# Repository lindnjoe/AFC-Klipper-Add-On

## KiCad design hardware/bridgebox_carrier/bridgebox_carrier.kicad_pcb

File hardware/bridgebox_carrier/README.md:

# BridgeBox carrier — KiCad project

The board described in
[`../../bambu_ams_bridge/docs/CARRIER_BOARD.md`](../../bambu_ams_bridge/docs/CARRIER_BOARD.md).
Read that first: it carries the reasoning, the current budget and the two
measured pinouts. This directory is the implementation.

Built against **KiCad 7**.

```
bridgebox_carrier.kicad_pro   project, netclasses and design rules
bridgebox_carrier.kicad_sch   schematic — generated, see below
bridgebox_carrier.kicad_pcb   board outline and stackup only
bridgebox.kicad_sym            symbols for the two modules
bridgebox.pretty/              footprints for the two modules
gen_project.py                writes the schematic and the symbol library
gen_pcb.py                    places and routes the board
route.py                      the tracks, as explicit polylines
geometry.py                   pad positions, shared by router and checker
verify_netlist.py             checks KiCad's netlist against the design
verify_wiring.py              checks the finished board against the proven pinout
check_placement.py            checks the placement for collisions
check_drc.py                  fast clearance and connectivity pre-check
finish_board.py               fills the ground plane, runs KiCad's real DRC
gen_bom.py                    the two BOMs
gen_cpl.py                    rewrites the placement file into CPL format
build.sh                      does all of it, in the one correct order
case/                         a two-piece printed case for the finished board
```

The case is its own project with its own checker and its own build; see
[`case/README.md`](case/README.md).

## Opening it

Open `bridgebox_carrier.kicad_pro`. Both the schematic and the board are
complete: placed, routed and checked. 367 mm of track, no vias and **no layer
changes at all** — B.Cu is an unbroken ground plane.

The board is 63 × 54 mm, two layers, 1 oz, laid out to the arrangement asked
for:

- **Left edge** — the Pico's USB and J1, the 24 V jack. The Pico is turned 90°
  so it runs inland from that edge with the USB overhanging it.
- **Bottom edge** — J2, the AMS 4-pin, a quarter turn round from them.
- Between them: the RS-485 module stands upright UNDER the Pico, logic pins up
  towards it and bus pins down towards J2, with the fuse in the band between.

**It used to be 84 × 58 mm.** Three things shrank it: the two A/B swap jumpers
came out once the bus wiring was settled on hardware, the module's pad columns
turned out to be 15 mm apart rather than the 0.7 in first assumed, and turning
the module upright moved it out from the Pico's right-hand side, which is what
the extra 21 mm of width had been for. Its bus pins now face J2 instead of
away from it, so A and B no longer lap the board — and the layer hop that used
to cost a slot in the ground plane went with them.

The M3 holes are **not** one per corner: the Pico's body runs the length of the
top edge and J2 owns the bottom middle, so most corners are already taken.

Mounting holes are placed in the board rather than drawn in the schematic,
which is normal for mechanical features — so if you ever re-import from the
schematic, leave "delete extra footprints" unticked or they will vanish.

Everything except the two modules comes from KiCad's stock libraries, including
`Molex_Micro-Fit_3.0_43045-0400_2x02_P3.00mm_Horizontal` for J2, so there is no
land pattern to draw by hand.

## Why the schematic is generated

The connectivity is the part that must not drift from the design document, so
it lives as a table — `NETS` in `gen_project.py` — rather than as geometry.
Regenerate with:

```sh
python3 gen_project.py
kicad-cli sch export netlist --output out/netlist.net bridgebox_carrier.kicad_sch
python3 verify_netlist.py
```

`verify_netlist.py` compares what KiCad *actually extracted* against that
table, pin for pin, and fails on a net that is split, merged or holding a pin
it should not. That matters because the schematic connects by label: a
mistyped label does not break the build, it silently makes two nets where
there should be one. The check is what lets this project be trusted without
opening the GUI.

Editing the schematic in KiCad is fine — but then it is the source, and
re-running the generator will overwrite it.

`verify_wiring.py` is narrower and runs LAST, after `finish_board.py` has
filled the zone and rewritten the file: it checks that the handful of pin
assignments established by measurement rather than by reading a silkscreen —
`GP0 → RXD`, `GP1 → TXD`, the A/B crossover, and J2's 24 V and GND — are the
ones on the pads the gerbers are plotted from. Every one of them is a place
where the obvious answer is wrong and the symptom of being wrong is a bus that
goes silent rather than one that misbehaves visibly.

`check_placement.py` does the same job for the board, comparing every
footprint's courtyard against every other one and against the mounting holes.
A render will not show you these: a mounting hole sitting inside the Pico's
outline just looks like a hole among a lot of pads. It found exactly that, plus
a 0.3 mm overlap between the Pico and the RS-485 module and a TVS sitting on
J2's body — none of which were visible by eye.

## What is still on you

Two things the project deliberately does not decide:

1. **A second pair of eyes on J2's pinout.** It is taken from Molex
   SD-43045-001 and the metered mating face, and it is the one mistake that
   puts 24 V on the transceiver.
2. **The remaining DRC warnings**, which are all cosmetic and all understood:

   | Count | Warning | Why it is left |
   |---|---|---|
   | 7 | `lib_footprint_issues` | this project's `fp-lib-table` lists only `bridgebox`; the stock libraries come from the global table on a normal install |
   | 3 | `silk_edge_clearance` | J2's body outline runs past the bottom edge, which is what a connector mating through that edge looks like; fabs clip silkscreen automatically |
   | 2 | `lib_footprint_mismatch` | the board's copy of the two custom footprints omits the library-only `version`/`generator` keys |

   **Zero errors:** no clearance violations, no unconnected pads, no footprint
   errors.

## Parts with no stock symbol

Both were measured, not taken from a datasheet:

- `RaspberryPi_Pico_THT` — 2×20, 0.1 in pitch, rows 0.7 in apart, pin 1 at the
  USB end.
- `MAX3485_Module_3L5R` — a 2×5 field with two positions empty. **Top view is
  three pins on the left (GND, A, B) and five on the right (EN, VCC, RXD, TXD,
  GND).** The underside reads mirrored; the footprint is the top view.
  0.1 in pitch down each column, columns **15 mm** apart — not the Pico's
  0.7 in. Measured on the part after a first revision built to 17.78 mm came
  back 2.8 mm too wide.

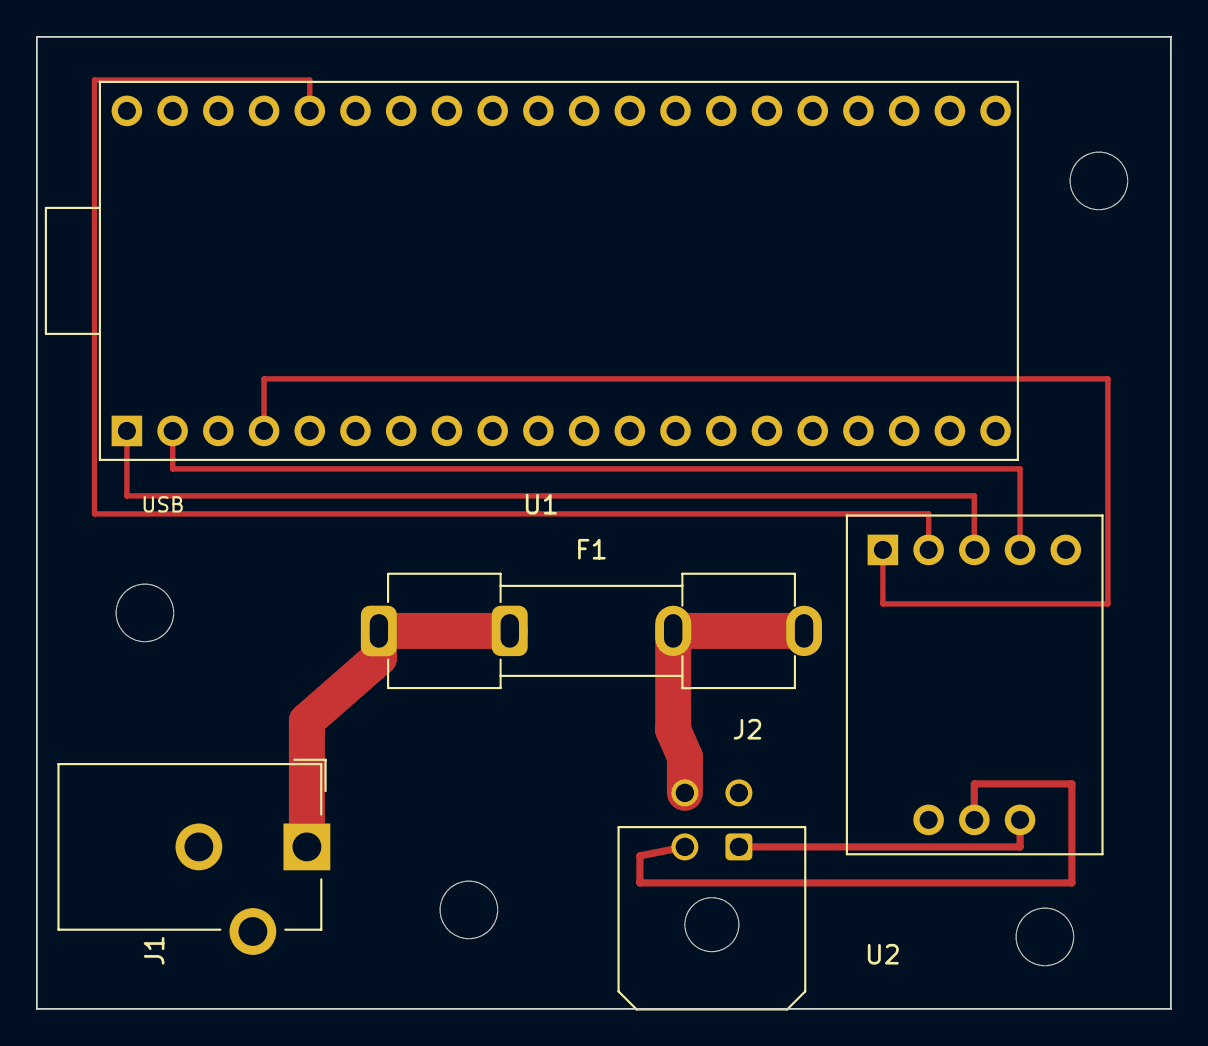
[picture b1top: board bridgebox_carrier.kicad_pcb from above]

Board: 2 copper layers, 63.0 x 54.0 mm, 9 parts (0 on the bottom side), 9 nets.

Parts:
F1: Fuseholder_Clip-5x20mm_Keystone_3512_Inline_P23.6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; Fuseholder_Clip-5x20mm_Keystone_3512_Inline_P23.62x7.27mm_D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
H1, H2, H3, H4: MountingHole_3.2mm_M3
J1: BarrelJack_CUI_PJ-102AH_Horizontal
J2: Molex_Micro-Fit_3.0_43045-0400_2x02_P3.00mm_Horiz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; Molex_Micro-Fit_3.0_43045-0400_2x02_P3.00mm_Horizontal
U1: RaspberryPi_Pico_THT
U2: MAX3485_Module_3L5R

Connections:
+3V3: U1.36, U2.2
+24V: F1.2, J2.4
+24V_IN: F1.1, J1.1
BUS_A: J2.1, U2.8
BUS_B: J2.2, U2.7
EN: U1.4, U2.1
GND: J1.2, J1.3, J2.3, U1.3, U1.8, U1.13, U1.18, U1.23, U1.28, U1.33, U1.38, U2.5, U2.6
RXD: U1.1, U2.3
TXD: U1.2, U2.4

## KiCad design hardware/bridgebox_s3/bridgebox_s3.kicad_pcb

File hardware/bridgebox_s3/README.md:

# BridgeBox S3 — KiCad project

The board described in
[`../../bambu_ams_bridge/docs/S3_BOARD.md`](../../bambu_ams_bridge/docs/S3_BOARD.md).
Read that first — it carries the reasoning. This directory is the
implementation, generated the same way the carrier is.

```
design.py          the whole design as data: parts, nets, S3 pin rules
verify_design.py   checks it against the real KiCad libraries, no KiCad needed
gen_project.py     writes the schematic, symbols embedded and flattened
verify_sch.py      reads the schematic BACK and rebuilds its netlist
fp_lib.py          footprint reader: pads, courtyards, rotation
check_placement.py courtyards, board edge, and the antenna keepout
gen_pcb.py         writes the board: footprints placed and netted, outline, zone
route.py           A* grid router, two layers, exact-geometry masks
check_drc.py       reads the BOARD back: clearance, ratsnest, containment
```

## Status

**Schematic done and proven. Board placed, routed and DRC-clean.**

```
verify_design.py    28 parts, 19 nets, 91 pins — every id resolved, every pad
                    accounted for, 7.0.11
gen_project.py      28 parts, 13 symbols embedded, 91 pin stubs
verify_sch.py       91 wires, 91 labels, 19 nets reconstructed — matches design.py
check_placement.py  74.1 x 65 mm, courtyards, keepout, and mating faces
gen_pcb.py          28 footprints, 19 nets, 91 pads netted, GND pour BOTH sides
build.sh            the chain in order; stops at the KiCad boundary
route.py            48 of 48, 589 mm, 51 vias — bus pair 0 mm on B.Cu
check_drc.py        clearance OK, every net one body, all copper on board
```

Nothing outstanding in the layout. `build.sh` (gerbers, drill, BOM, CPL) is the
remaining step, and three measurements gate ordering — see **Next**.

### A connector that faces its own board

J2 sat at `rot 0` for the whole of this board's life. At `rot 0` this
footprint's mating face points at local −y, so placed at y = 52 the opening
was at board y = **43.08, aimed into the board**, with 43 mm of PCB in front of
it. It routed, it passed DRC, it plotted like a finished board, and no cable
could ever have gone into it.

Nothing here could see that, because it is not a copper question. And the
courtyard actively misleads: its +y overhang is covering the second pad row,
not mating clearance, which is what made the *x* extent look like it set the
board width. The **F.Fab body outline** is what answers it — the shell spans
y −8.92…0.99 with the pads at y 0 and 3, so the body is on the −y side and the
opening is its far end.

`design.MATING` now declares each connector's mating axis and whether it may
protrude, and `check_placement.py` maps that through the placement rotation and
insists it lands on an edge:

```
J1 faces the bottom edge at (10.00, 70.70) -- protrudes (5.70 mm)
J2 faces the bottom edge at (68.50, 65.00) -- flush (0.00 mm)
J3 faces the left edge at (0.50, 40.05) -- flush (0.50 mm)
```

Put J2 back at `rot 0` and it fails with *"mating face … is 5.6 mm inside the
outline — no cable reaches it"*, which is how the check was confirmed to be
worth having rather than merely passing.

J1 is allowed to protrude because a barrel jack is meant to: that is how it
meets a panel. J2 and J3 are flush, so a case wall can sit against them. Both
cables now leave the bottom and left faces, and the board lost the 3 mm of
width that only existed because J2 was measured on the wrong axis: 80 → 77.1 →
**74.1**.

### Route order is a design decision, not a loop variable

Nets were routed in alphabetical order, which is not an order at all: whoever
goes first gets the corridor. `+24V` is the widest net on the board at 2 mm, it
sorts first, and it took the channel down to J2 before `BUS_B` — five letters
later — ever asked. BUS_B then had nowhere to go on F.Cu and spent 18 mm on the
back, underneath its own partner's return path.

A person laying this out routes the pair first and threads power around it,
because the pair is what the board is for. Doing that:

```
                 BUS_A            BUS_B           total copper
alphabetical     73 mm, 0 back    42 mm, 18 back      627 mm
pair first       33 mm, 0 back    41 mm,  0 back      583 mm
```

Both halves of the bus are now entirely on F.Cu over unbroken pour, and the
board uses 44 mm *less* copper. `route.py` reports what the priced nets actually
did on every run, which is how the 18 mm was noticed rather than shipped.

### The pad-coverage check, and the three faults it found

`verify_design.py` asks "does every pin `design.py` names exist?". It could not
ask the question that matters more — **is there a pad on the board that
`design.py` never mentions?** That is the shape of a wrong symbol, and a wrong
symbol resolves perfectly. Adding the check found three faults on a board that
had already routed and passed DRC:

| | was | is |
|---|---|---|
| `D2` | `Device:D_TVS`, a **two**-pin symbol in a three-pad SOT-23 | `Diode:SM712_SOT23`; pin `common` to GND |
| `R2B` | fail-safe bias **pull-down connected to nothing** | `R2B.2` to GND |
| `J3` | USB-C shell floating | `SHIELD` to GND |

The SM712 is an RS-485 clamp whose third pin is where a surge is supposed to
*go*; without it the part cannot do its only job. `S3_BOARD.md` states the bias
rule outright — "biasing A up to VCC and **B down to GND**" — and the down half
was not connected, so an idle bus had no defined differential at all. None of
these is visible in a netlist, a DRC or a plot. All three are invisible until
something counts pads.

Pins that are *meant* to float are now **declared** in `design.py`'s
`NO_CONNECT`, with a reason each, rather than filtered out. An undeclared
floating pad is a question nobody asked; a declared one is a decision. The check
also reports a declaration that has gone stale.

## Two layers, and the reason is duller than first written

The first version of this README said the USB-C flip pairs were **geometrically**
unroutable on one layer — "tying A6 to B6 means passing between pads on a 0.5 mm
pitch", "no placement fixes that", "which is why every USB-C design has a second
routing layer". That was confident and it was wrong.

The footprint (`HRO TYPE-C-31-M-12`) puts all sixteen contacts in **one row**:

```
A1/B12  A4/B9   B8    A5    B7    A6    A7    B6    A8    B5   A9/B4  A12/B1
 -3.25  -2.45  -1.75 -1.25 -0.75 -0.25  0.25  0.75  1.25  1.75  2.45   3.25
```

Nothing is threaded between anything — each pad escapes straight out, and the
DP/DM crossing happens away from the connector. What actually blocked it was the
router, twice:

* **the pads sat half a grid cell off the grid.** 0.5 mm pitch from an origin
  at y = 40.0 puts every pad centre on an odd multiple of 0.25. The escape
  clears its neighbour by 0.025 mm when perfectly centred, so half a cell of
  offset loses it. `PLACE["J3"]` is now `40.05`.
* **obstacles were rasterised then dilated.** That quantises a pad EDGE to
  ±0.05 mm — twice the entire margin. And `40.15 / 0.1` is `401.4999999999999`
  in binary floating point, so one pad grew a whole cell in one direction only.
  `route.py` now keeps obstacles as geometry and tests exact distances.

The board does still want two layers: one gets 29 connections, two gets 48. But
that is congestion and fan-out — an ordinary reason — and the interesting claim
that replaced it was never true. B.Cu is signal-and-pour, F.Cu gains a pour of
its own, and the two are stitched.

Because the tightest gap on this board is a quarter of a grid cell, the router
cannot be the last word on whether its own answer is legal. `check_drc.py`
re-reads the finished `.kicad_pcb` at full floating-point precision and reports
the tightest track-to-pad gap: **0.200 mm**, exactly the rule, no margin to
spare and none borrowed.

### What check_drc.py caught that nothing else would

`F1` was a 5×20 mm cartridge in a clip holder — and a clip holder has **two pads
numbered 1 and two numbered 2**, one pair per clip. `route.py` looked pads up by
number and returned the first match, so 24 V reached one half of each terminal
and left the other a floating rectangle. It routes cleanly, it passes every
clearance rule, it looks finished on screen, and it is an open circuit through
the fuse. Only the connectivity check sees it. `Board.pads_of` now returns every
pad with a number, and each is its own target.

The fuse is a 2920 PPTC now (see `design.py`), which is what prompted looking.

## The libraries

Not committed — ~315 MB, and the reproducible part is the *tag*, not the bytes:

```
git clone --depth 1 -b 7.0.11 https://gitlab.com/kicad/libraries/kicad-symbols.git ksym
git clone --depth 1 --filter=blob:none --sparse -b 7.0.11 \
    https://gitlab.com/kicad/libraries/kicad-footprints.git kfp
cd kfp && git sparse-checkout set RF_Module.pretty Package_SO.pretty \
    Package_TO_SOT_SMD.pretty Connector_USB.pretty Capacitor_SMD.pretty \
    Resistor_SMD.pretty Diode_SMD.pretty Inductor_SMD.pretty \
    Button_Switch_SMD.pretty Connector_BarrelJack.pretty Fuse.pretty \
    Connector_Molex.pretty MountingHole.pretty
```

Then `KICAD_LIBS=/path/to/parent python3 verify_design.py`, or drop both
checkouts in `./libs/`, or point it at a system KiCad install — it handles all
three layouts.

## Why pins are addressed by NAME

The carrier's generator hardcodes pin numbers, which is safe when you can see
the library while writing it. This design was drafted without one, and the
libraries then corrected three things that would each have produced a board
that generates cleanly and is wrong:

| assumed | actual |
|---|---|
| `Interface_UART:MAX3485E` | no such symbol — it is `MAX3485` |
| `Connector:USB_C_Receptacle_USB2.0` | `USB_C_Receptacle_USB2.0_16P` |
| TPS54202DDC = BOOT/VIN/EN/GND/FB/SW | **GND/SW/VIN/FB/EN/BOOT** |

That last one is the whole argument. Addressed by number, the buck's netlist
would have been silently wrong in five places; addressed by name,
`verify_design.py` resolves it from the symbol and the mistake cannot happen.
Pin *names* are also inherited — `MAX3485` extends `MAX481E` and `TPS54202DDC`
extends `TPS54302`, so a reader that stops at the top level sees a part with no
pins at all and validates nothing.

Parts whose pins have no names (`Device:R`, `Device:C`, the barrel jack, the
fuse — all `~`) are addressed by number, and the resolver takes either.

## Next

1. ~~`gen_project.py` — symbols + schematic~~ done
2. ~~`gen_pcb.py` / `route.py` — placement and tracks~~ done
3. ~~`check_placement.py`, `check_drc.py` — the pure-Python pre-checks~~ done
4. `build.sh` — gerbers, drill, BOM, CPL

Before ordering, and each is one measurement, from `docs/S3_BOARD.md`:

* the breakout's termination and bias values, metered;
* **the 24 V draw during a feed, with a clamp meter.** This one got sharper
  when the fuse became a PPTC: the 2920 part holds 2.6 A at 30 V and derates
  to roughly 1.9 A at 60 C, against a 3 A budget that has never been measured.
  It now decides a part, not just a trace width;
* whether an S3 holds the poll cadence with WiFi associated.

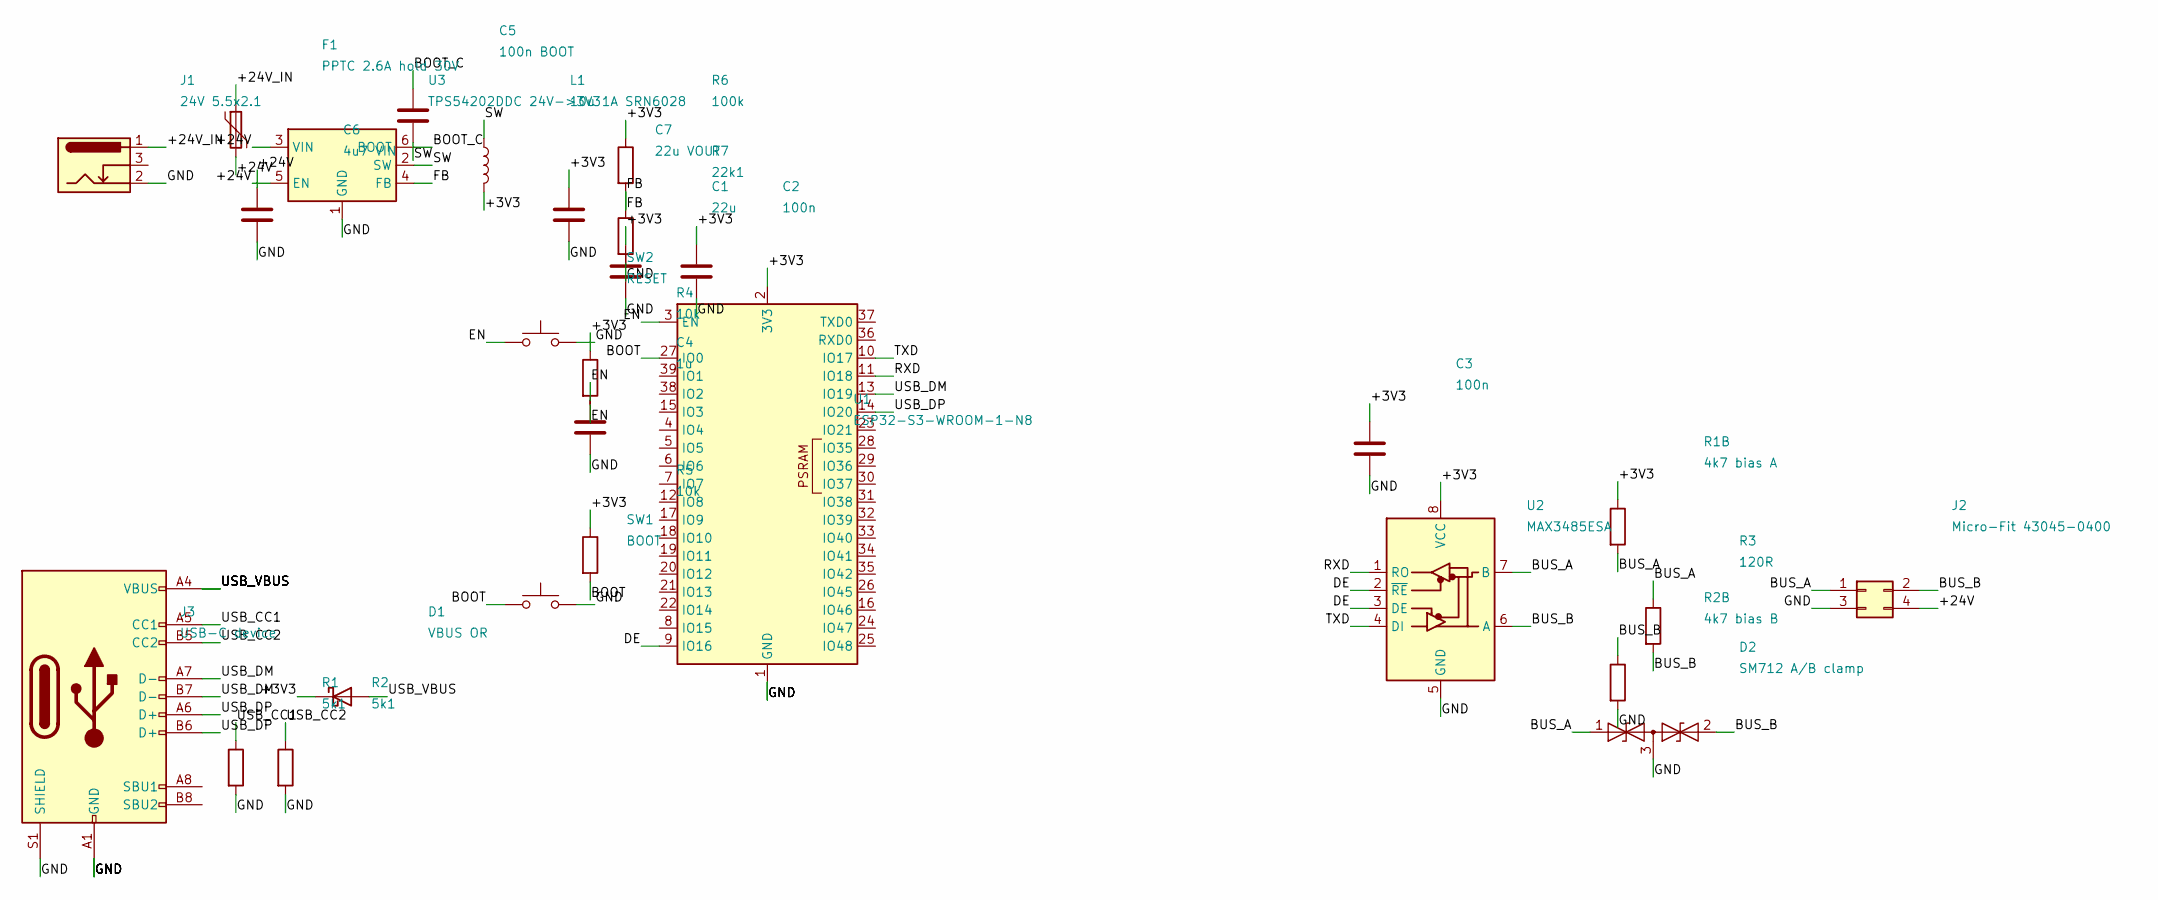
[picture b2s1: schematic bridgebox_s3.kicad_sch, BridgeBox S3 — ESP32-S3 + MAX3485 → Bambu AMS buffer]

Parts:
C1: 22u; C_0805_2012Metric
C2, C3: 100n; C_0402_1005Metric
C4: 1u; C_0402_1005Metric
C5: 100n BOOT; C_0402_1005Metric
C6: 4u7 VIN; C_0805_2012Metric
C7: 22u VOUT; C_0805_2012Metric
D1: VBUS OR; D_SOD-123
D2: SM712 A/B clamp; SOT-23
F1: PPTC 2.6A hold 30V; Fuse_2920_7451Metric
J1: 24V 5.5x2.1; BarrelJack_CUI_PJ-102AH_Horizontal
J2: Micro-Fit 43045-0400; Molex_Micro-Fit_3.0_43045-0400_2x02_P3.00mm_Horizontal
J3: USB-C device; USB_C_Receptacle_HRO_TYPE-C-31-M-12
L1: 10u 1A SRN6028; L_Bourns-SRN6028
R1, R2: 5k1; R_0402_1005Metric
R1B: 4k7 bias A; R_0402_1005Metric
R2B: 4k7 bias B; R_0402_1005Metric
R3: 120R; R_0805_2012Metric
R4, R5: 10k; R_0402_1005Metric
R6: 100k; R_0402_1005Metric
R7: 22k1; R_0402_1005Metric
SW1: BOOT; SW_SPST_B3U-1000P
SW2: RESET; SW_SPST_B3U-1000P
U1: ESP32-S3-WROOM-1-N8; ESP32-S3-WROOM-1
U2: MAX3485ESA; SOIC-8_3.9x4.9mm_P1.27mm
U3: TPS54202DDC 24V->3V3; SOT-23-6

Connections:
+3V3: C1.1, C2.1, C3.1, C7.1, D1.1 (K), L1.2, R1B.1, R4.1, R5.1, R6.1, U1.2 (3V3), U2.8 (VCC)
+24V: C6.1, F1.2, J2.4, U3.3 (VIN), U3.5 (EN)
+24V_IN: F1.1, J1.1
BOOT: R5.2, SW1.1, U1.27 (IO0)
BOOT_C: C5.1, U3.6 (BOOT)
BUS_A: D2.1 (A1), J2.1, R1B.2, R3.1, U2.7 (B)
BUS_B: D2.2 (A2), J2.2, R2B.1, R3.2, U2.6 (A)
DE: U1.9 (IO16), U2.2 (~RE), U2.3 (DE)
EN: C4.1, R4.2, SW2.1, U1.3 (EN)
FB: R6.2, R7.1, U3.4 (FB)
GND: C1.2, C2.2, C3.2, C4.2, C6.2, C7.2, D2.3 (common), J1.2, J2.3, J3.A1 (GND), J3.A12 (GND), J3.B1 (GND), J3.B12 (GND), J3.S1 (SHIELD), R1.2, R2.2, R2B.2, R7.2, SW1.2, SW2.2, U1.1 (GND), U1.40 (GND), U1.41 (GND), U2.5 (GND), U3.1 (GND)
RXD: U1.11 (IO18), U2.1 (RO)
SW: C5.2, L1.1, U3.2 (SW)
TXD: U1.10 (IO17), U2.4 (DI)
USB_CC1: J3.A5 (CC1), R1.1
USB_CC2: J3.B5 (CC2), R2.1
USB_DM: J3.A7 (D-), J3.B7 (D-), U1.13 (IO19)
USB_DP: J3.A6 (D+), J3.B6 (D+), U1.14 (IO20)
USB_VBUS: D1.2 (A), J3.A4 (VBUS), J3.A9 (VBUS), J3.B4 (VBUS), J3.B9 (VBUS)

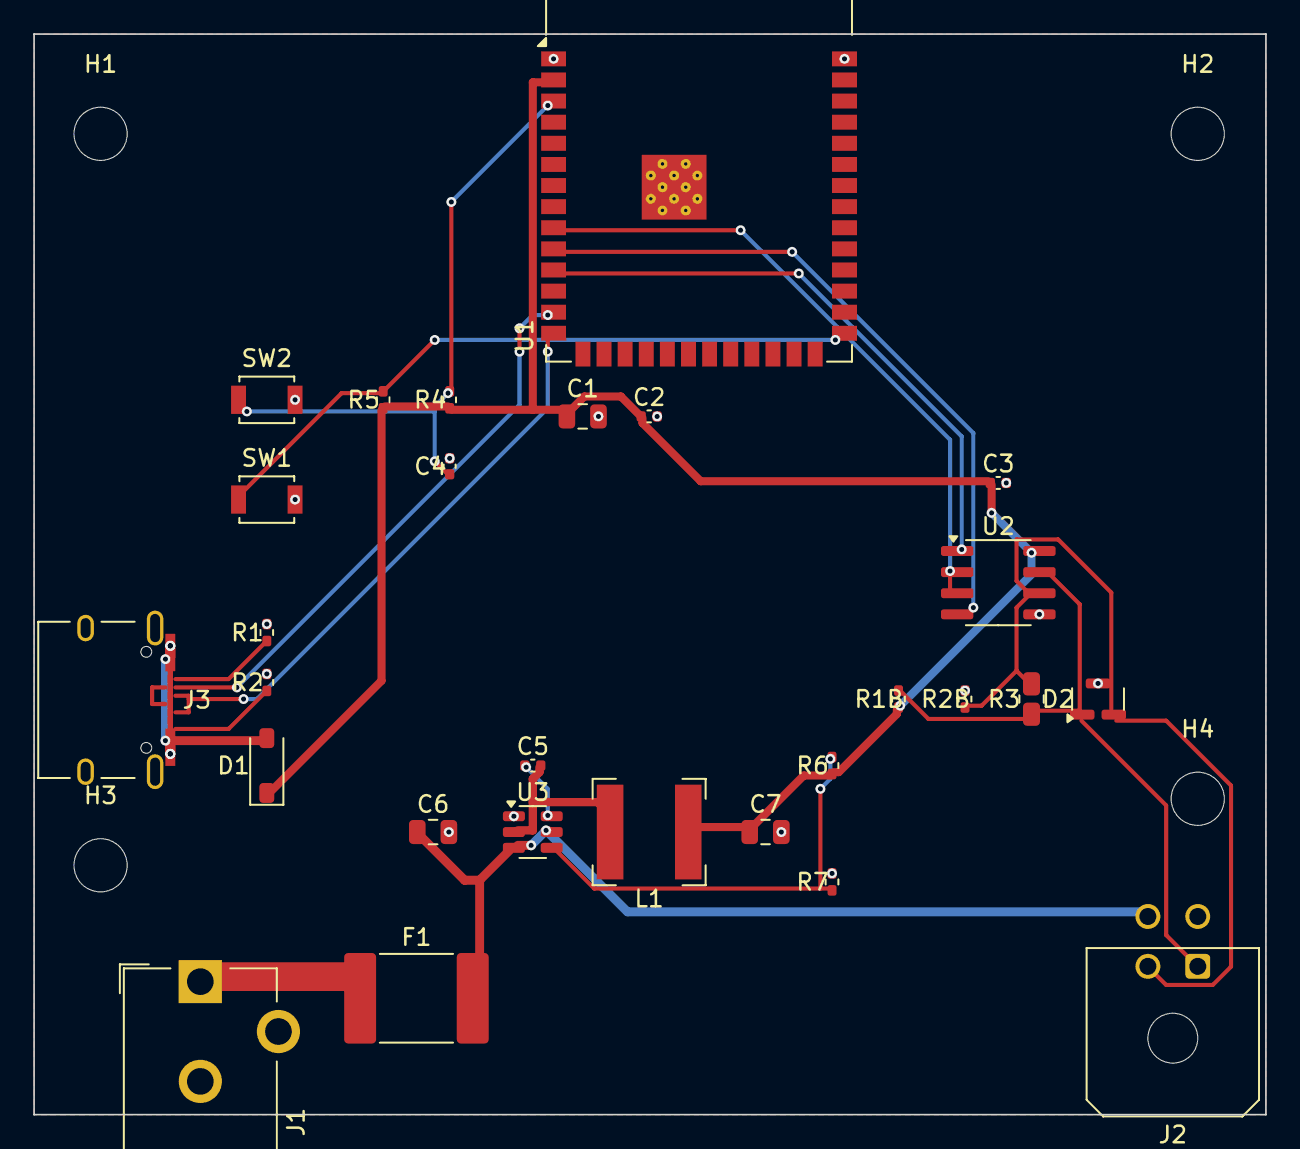
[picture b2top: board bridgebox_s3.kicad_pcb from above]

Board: 2 copper layers, 74.1 x 65.0 mm, 32 parts (0 on the bottom side), 19 nets.

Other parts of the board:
H1, H2, H3, H4: M3; MountingHole_3.2mm_M3

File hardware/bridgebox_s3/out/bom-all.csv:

Comment,Designator,Footprint,LCSC Part #
100k,R6,R_0402_1005Metric,
100n,"C2,C3",C_0402_1005Metric,
100n BOOT,C5,C_0402_1005Metric,
10k,"R4,R5",R_0402_1005Metric,
10u 1A SRN6028,L1,L_Bourns-SRN6028,
120R,R3,R_0805_2012Metric,
1u,C4,C_0402_1005Metric,
22k1,R7,R_0402_1005Metric,
22u,C1,C_0805_2012Metric,
22u VOUT,C7,C_0805_2012Metric,
24V 5.5x2.1,J1,BarrelJack_CUI_PJ-102AH_Horizontal,
4k7 bias A,R1B,R_0402_1005Metric,
4k7 bias B,R2B,R_0402_1005Metric,
4u7 VIN,C6,C_0805_2012Metric,
5k1,"R1,R2",R_0402_1005Metric,
ESP32-S3-WROOM-1-N8,U1,ESP32-S3-WROOM-1,
MAX3485ESA,U2,SOIC-8_3.9x4.9mm_P1.27mm,
Micro-Fit 43045-0400,J2,Molex_Micro-Fit_3.0_43045-0400_2x02_P3.00mm_Horizontal,
PPTC 2.6A hold 30V,F1,Fuse_2920_7451Metric,
SM712 A/B clamp,D2,SOT-23,
Schottky 30V 1A SOD-123 (BAT60A / SS13),D1,D_SOD-123,
TPS54202DDC 24V->3V3,U3,SOT-23-6,
USB-C receptacle 16P SMD (HRO TYPE-C-31-M-12),J3,USB_C_Receptacle_HRO_TYPE-C-31-M-12,
tactile SPST 4.5x4.5mm SMD (B3U-1000P),"SW1,SW2",SW_SPST_B3U-1000P,

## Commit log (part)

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2024-10-19 Added save state when changing lane, added addition move to and from hub
2024-10-20 Changing Buffer_Type to Buffer_Name
2024-10-23 Minor updates from merge
2024-10-24 Replacing lookup_object for AFC and referencing self.AFC object
2025-04-07 Fixing resume function so its closer to klipper restore gcode state when restoring extruder position
2025-10-20 Support AMS shared sensors and optional hub switch pin
2025-10-20 Fix lane lookup while printing
2025-10-20 Revert "Fix current lane lookup during prints"
2025-10-20 Allow lane lookup while printer state reports printing
2025-10-20 Remove external deadband command registration
2025-10-20 Broaden lane detection during active jobs
2025-10-20 Add AMS unit installation support
2025-10-20 Normalize shared AMS load sensor detection
2025-10-20 Ensure AMS runout clears spool assignment
2025-10-20 Reset spool assignment when AMS lane empties
2025-10-20 Guard AMS shared sensor clears to preserve next spool assignment
2025-10-21 Defer shared prep clears until debounce completes
2025-10-21 Improve AMS shared sensor handling
2025-10-21 Ensure AMS lanes clear spool assignments on unload
2025-10-21 Restore active spool after idle lane updates
2025-10-21 Improve prep runout detection for assigned lanes
2025-10-22 Repackage AMS overrides as bundled modules
2025-10-22 Allow hubs without physical switch pins
2025-10-22 Revert "Direct update"
2025-10-22 Add virtual AMS tool sensor registration
2025-10-22 Fix AMS virtual sensor log message
2025-10-23 Add deadband handling for extruder temperature
2025-10-23 Add AMS integration helpers for AFC
    Implement AMS integration helpers for Armored Turtle AFC, including virtual filament sensor and runout handling.
2025-10-23 Enhance lane tool filament reporting and patch AFCLane
    Added a method to report the tool filament state for a lane and patched the AFCLane class to support AMS virtual sensors.
2025-10-24 Adjust temperature tolerance calculation
2025-10-25 Add AMS integration helpers for AFC
    Implement AMS integration helpers for Armored Turtle AFC, including virtual runout and filament sensor classes, and synchronization logic with OpenAMS.
2025-10-25 Add AMS integration helpers for Armored Turtle AFC
    This file contains integration helpers for the Armored Turtle AFC system, including classes for virtual runout and filament sensors, as well as synchronization with OpenAMS. The code also implements 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
2025-10-25 Add AFC_AMS integration helpers for virtual sensors
    This commit introduces the AFC_AMS.py file, which contains integration helpers for the Armored Turtle AFC. It includes classes and methods for managing virtual sensors, handling filament detection, a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
2025-10-25 Refactor switch_pin assignment and improve formatting
2025-10-26 Enhance lane management and notifications
    Added methods to resolve lane for spool and get latest lane snapshot for spool. Updated notify_runout_detected to include lane name.
2025-10-27 Simplify lane tool latch update logic
    Removed checks for lane_obj in lane tool latch updates.
2025-10-27 Handle switch_pin assignment with error handling
2025-10-27 Update AFC_AMS.py to current upstream version
2025-10-27 Update AMS ASCII art banner
2025-10-27 Comment out AFC_led configuration section
2025-10-28 Change event handler from 'connect' to 'ready'
2025-11-01 Add OpenAMS calibration support to unit prompts
2025-11-01 Clarify OpenAMS calibration prompt text
2025-11-01 Persist initial OpenAMS calibration results
2025-11-01 Persist OpenAMS PTFE calibration directly to oamsc.cfg
2025-11-01 Persist OpenAMS PTFE calibration via wrapper command
2025-11-01 Simplify OpenAMS PTFE calibration persistence
2025-11-01 Update for OpenAMS unit calibration with cfg saving
2025-11-01 Limit OpenAMS all-lanes busy check to unit extruder
2025-11-01 Persist OpenAMS PTFE calibration to hub configs
2025-11-01 Tweak PTFE calibration prompt wording
2025-11-01 Fix OpenAMS PTFE calibration command registration
2025-11-01 Use ConfigRewrite for OpenAMS calibration persistence
2025-11-01 Simplify OpenAMS calibration persistence
2025-11-01 Fix OpenAMS hub HES config persistence
2025-11-01 Run OpenAMS calibrations directly per lane
2025-11-01 Restore OpenAMS calibration command dispatch
2025-11-01 Scope OpenAMS calibrations to afcAMS
2025-11-01 Simplify OpenAMS calibration prompts
2025-11-01 Guard OpenAMS calibration prompts when lanes missing
2025-11-01 Fix OpenAMS calibration prompts import
2025-11-01 Guard hub HES rewrites against missing baseline values
2025-11-02 Refactor OpenAMS calibration prompts
2025-11-02 Align OpenAMS helper with upstream and retain calibration flow
2025-11-02 Optimize OpenAMS integration code
    Refactor and optimize the OpenAMS integration code for better performance and readability.
2025-11-02 Optimize AMS integration helpers for performance
    Refactored AMSHardwareService and AMSRunoutCoordinator for improved performance and maintainability. Added caching for reactor reference and optimized status update mechanism.
2025-11-03 Refactor OpenAMS integration helpers and comments
2025-11-06 Add event system and refactor lane management
    Refactor to implement event system for lane state changes and enhance lane registry usage.
2025-11-06 Fix clog follower reenable
2025-11-07 Fix logging format for registered lane information
2025-11-08 Revert "Revert "Multi extruder""
2025-11-08 Implement G-code macros for filament control
    Added multiple G-code macros for filament management and tool changes.
2025-11-08 Update custom load/unload commands in configuration
2025-11-08 Refactor OpenAMS hardware detection logic
    Refactor OpenAMS integration to check for hardware presence during handle_ready instead of config load. Update logging for better clarity on hardware detection.
2025-11-09 Update to Event handling instead of constant polling of sensors
2025-11-14 Implement event-driven sensor handling in AFC_OpenAMS
    Refactor polling logic to event-driven model for sensor changes.
2025-11-14 Implement lane empty marking for runout
    Add logic to mark lane as empty during runout process.
2025-11-15 Implement OpenAMS PTFE calibration commands
    Added commands for OpenAMS PTFE calibration and updated calibration menus.
2025-11-15 Update custom_load_cmd for lanes in AFC_AMS_1.cfg
    Fix the load command to be more inline with AFC. The Openams implementation has been converted to a lane based setup to match.
2025-11-15 Implement event system and integrate with AMS service
    Added an event system to handle lane state changes, allowing for efficient event publishing and subscriber management. Updated AMSHardwareService to utilize LaneRegistry for lane lookups and integrat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
2025-11-15 Enhance runout detection and logging in AFC_OpenAMS
    Refactor runout handling logic to differentiate between same-FPS and cross-FPS scenarios. Update logging messages for clarity.
2025-11-15 Implement lane tool loading and unloading logic
    Added logic to clear tool_loaded state for lanes on the same or different extruders when a new lane loads. This ensures proper synchronization and unloading behavior across lanes.
2025-11-15 Implement unsync for virtual sensor extruders
    Added handling for virtual sensor extruders to unsync before clearing tool_loaded.
2026-02-20 Add support for custom load and unload sequences
2026-02-20 Implement unit-specific TD-1 workflow overrides
    Added unit-specific overrides for TD-1 capture and prep workflows.
2026-02-20 Clarify temperature setting comments in AFC.py
    Updated comments for clarity on temperature setting logic.
2026-02-21 Update CHANGELOG for version 2026-02-21
    Added new features, refactored existing code, and removed outdated configurations.
2026-02-21 Update CHANGELOG for lane hooks and button handling
    Updated changelog to reflect changes in lane handling and button functionality.
2026-02-24 Update CHANGELOG for 2026-02-23 release
    Updated changelog date and added new features and fixes.
2026-03-29 Add configuration file for AFC ACE 1 setup
2026-04-23 Update AFC_ACE.py from lindnjoe/AFC-Toolchanger main branch
    Drop-in replacement with improvements that are compatible with our
    current AFC/AFC_unit.py/AFC_lane.py hook infrastructure:
    - Implements prep_capture_td1 / capture_td1_data unit hooks for ACE-native
    TD-1 capture via feed_filament (no stepper moves)
    - TD-1 capture is now triggered from prep_post_load when filament reaches
    the hub, eliminating the need for the base stepper-based capture path
2026-06-02 [feat]: Initial support for Snapmaker U1 machine (#721)
    Updates to allow AFC to work on Snapmaker U1
    - Added a signature check for trapq_append_sig c function since Snapmaker
    klipper add another parameter to this function call. When detected a zero
    is appended to a tuple before calling and unpacking args for trapq_append
    function.
    - Added ability to always force override T(n) mappings with force_assign_map
2026-06-09 (feat): Adding detecting toolhead runout for standalone toolhead for toolchangers (#730)
    Adding detecting toolhead runout for standalone toolheads
    - Fixed infinite runout to work correctly with toolchangers
    - Added parking and wiping when waiting for next extruder temperature when infinite runout occurs for toolchangers
2026-06-15 Add AFC FPS Buffer Configuration
    This file configures the FPS buffer drivers, replacing mechanical switches with an analog pressure sensor for filament feed rate adjustment.
2026-06-15 Add switch_pin configuration to AFC hubs
2026-06-15 Add AFC_Ace_1_combined.cfg template
2026-06-19 (feat): Adding support for HTLF2-Claymore Unit (#733)
    - Added full support for the HTLF2-Claymore unit type, including dedicated installation menu/config workflow.
    - Added Claymore board type selection (cycled via option H) and Claymore-specific system menu/installation messaging.
    ---------
2026-06-21 (fix) Fixes #734, correctly sets toolhead leds during PREP for toolchangers (#737)
    * Fixes #734, correctly sets toolhead leds for toolchangers
    - Fix includes setting toolhead leds correctly for standalone toolheads
2026-06-21 (feat): Adding ability to add custom extruder name for AFC_extruder (#740)
    * Added support for giving AFC’s `AFC_extruder` config section a custom name (not limited to `extruder(x)`).
    * Added/extended `extruder_name` configuration to use a custom toolhead extruder identifier (`extruder_name` must match the toolhead’s extruder name when not using `extruder(x)`).
    * Updating U1 template so that AFC_extruder names match stock names of e(0-1)
2026-06-23 First go and removing some compat code
2026-06-25 Adding unit specific load/unload methods to OpenAMS unit - Added a check during load/unload to call the unit specific load/unload method instead of doing the normal sequence. Custom lane unload/load 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
2026-06-25 Commenting out custom_load/unload_cmd to lanes
2026-06-26 Combined AFC_FPS into AFC_buffer file
2026-06-26 Removing compat and FPS files
2026-06-26 Renaming oams to AFC_OAMS
2026-06-27 Bringing in changes from joebol
2026-06-27 Fixing move_e_pos call
2026-06-28 (feat): Adding flag so that standalone toolhead will purge after being loaded the first time with switching to tool (#744)
    - Adding flag so that standalone toolhead will purge after being loaded the first time with switching to tool
    - This is needed so that nozzle will be primed correctly and previous color gets flushed out
2026-06-29 (fix): Updating code to only enable/disable motor current, sync and disable when needed (#746)
    * Updating code to only enable/disable motor current, sync and disable when needed
    - Fixes #726
    - Put a guard for syncing to extruder and setting motor current so that these
    actions are only performed when needed. This help speed up toolchanger
    swapping toolheads. Before everything had it current set even when not needed.
    - Put a check in to only disable steppers if they are enabled.
